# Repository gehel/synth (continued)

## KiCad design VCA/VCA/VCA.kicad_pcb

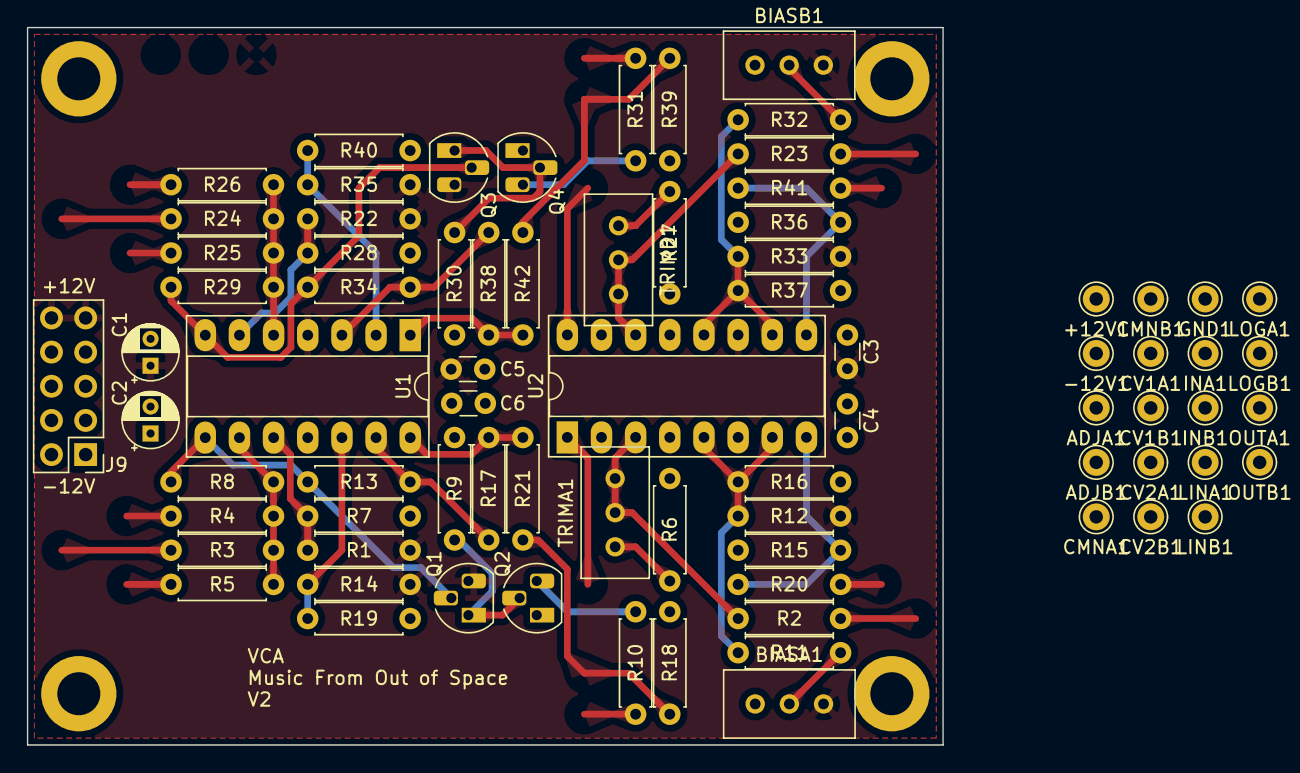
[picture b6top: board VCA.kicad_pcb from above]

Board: 4 copper layers, 68.1 x 53.3 mm, 82 parts (0 on the bottom side), 45 nets.

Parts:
+12V1: Conn_01x01_Pin; Pin_D1.0mm_L10.0mm
-12V1: Conn_01x01_Pin; Pin_D1.0mm_L10.0mm
ADJA1: Conn_01x01_Pin; Pin_D1.0mm_L10.0mm
ADJB1: Conn_01x01_Pin; Pin_D1.0mm_L10.0mm
BIASA1: 100K; Potentiometer_Bourns_3296W_Vertical
BIASB1: 100K; Potentiometer_Bourns_3296W_Vertical
C1, C2: 10uF; CP_Radial_D4.0mm_P2.00mm
C3, C4, C5, C6: 100nF; C_Disc_D3.0mm_W1.6mm_P2.50mm
CMNA1: Conn_01x01_Pin; Pin_D1.0mm_L10.0mm
CMNB1: Conn_01x01_Pin; Pin_D1.0mm_L10.0mm
CV1A1, CV1B1, CV2A1, CV2B1: Conn_01x01_Pin; Pin_D1.0mm_L10.0mm
GND1: Conn_01x01_Pin; Pin_D1.0mm_L10.0mm
H1, H2, H3, H4: MountingHole_Pad; MountingHole_3.2mm_M3_DIN965_Pad
INA1: Conn_01x01_Pin; Pin_D1.0mm_L10.0mm
INB1: Conn_01x01_Pin; Pin_D1.0mm_L10.0mm
J9: Conn_02x05_Odd_Even; PinHeader_2x05_P2.54mm_Vertical
LINA1: Conn_01x01_Pin; Pin_D1.0mm_L10.0mm
LINB1: Conn_01x01_Pin; Pin_D1.0mm_L10.0mm
LOGA1: Conn_01x01_Pin; Pin_D1.0mm_L10.0mm
LOGB1: Conn_01x01_Pin; Pin_D1.0mm_L10.0mm
OUTA1: Conn_01x01_Pin; Pin_D1.0mm_L10.0mm
OUTB1: Conn_01x01_Pin; Pin_D1.0mm_L10.0mm
Q1, Q3: 2N3904; TO-92_HandSolder
Q2, Q4: 2N3906; TO-92_HandSolder
R1, R2, R3, R4, R5, R14, R17, R19, R22, R23, R24, R25, R26, R35, R38, R40: 100K; R_Axial_DIN0207_L6.3mm_D2.5mm_P7.62mm_Horizontal
R6, R27: 150R; R_Axial_DIN0207_L6.3mm_D2.5mm_P7.62mm_Horizontal
R7, R8, R13, R28, R29, R34: 2K; R_Axial_DIN0207_L6.3mm_D2.5mm_P7.62mm_Horizontal
R9, R30: 120K; R_Axial_DIN0207_L6.3mm_D2.5mm_P7.62mm_Horizontal
R10, R18, R31, R39: 20K; R_Axial_DIN0207_L6.3mm_D2.5mm_P7.62mm_Horizontal
R11, R32: 2M; R_Axial_DIN0207_L6.3mm_D2.5mm_P7.62mm_Horizontal
R12, R33: 470K; R_Axial_DIN0207_L6.3mm_D2.5mm_P7.62mm_Horizontal
R15, R36: 4.7K; R_Axial_DIN0207_L6.3mm_D2.5mm_P7.62mm_Horizontal
R16, R37: 47K; R_Axial_DIN0207_L6.3mm_D2.5mm_P7.62mm_Horizontal
R20, R41: 1K; R_Axial_DIN0207_L6.3mm_D2.5mm_P7.62mm_Horizontal
R21, R42: 30K; R_Axial_DIN0207_L6.3mm_D2.5mm_P7.62mm_Horizontal
TRIMA1: 2K; Potentiometer_Bourns_3296W_Vertical
TRIMB1: 2K; Potentiometer_Bourns_3296W_Vertical
U1: TL084; DIP-14_W7.62mm_Socket_LongPads
U2: LM13700; DIP-16_W7.62mm_Socket_LongPads

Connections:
+12V: +12V1.1, BIASA1.1, BIASB1.1, C1.1, C3.1, C5.1, J9.9, J9.10, Q1.3 (C), Q3.3 (C), R1.1, R12.1, R14.1, R22.1, R33.1, R35.1, U1.4 (V+), U2.11 (V+)
-12V: -12V1.1, BIASA1.3, BIASB1.3, C2.2, C4.2, C6.2, J9.1, J9.2, R9.1, R15.1, R18.1, R30.1, R36.1, R39.1, U1.11 (V-), U2.6 (V-)
ADJA: ADJA1.1, R5.1
ADJB: ADJB1.1, R26.1
CMNA: CMNA1.1, U2.1
CMNB: CMNB1.1, U2.16
CV1A: CV1A1.1, R3.1
CV1B: CV1B1.1, R24.1
CV2A: CV2A1.1, R4.1
CV2B: CV2B1.1, R25.1
GND: C1.2, C2.1, C3.2, C4.1, C5.2, C6.1, GND1.1, H1.1, H2.1, H3.1, H4.1, J9.3, J9.4, J9.5, J9.6, J9.7, J9.8, Q2.1 (E), Q4.1 (E), R6.1, R7.2, R16.2, R19.2, R27.1, R28.2, R37.2, R40.2, U2.4 (-), U2.13 (-)
INA: INA1.1, R2.1
INB: INB1.1, R23.1
LINA: LINA1.1, R18.2, R21.1
LINB: LINB1.1, R39.2, R42.1
LOGA: LOGA1.1, R10.1
LOGB: LOGB1.1, R31.1
unnamed: BIASA1.2, R11.1
unnamed: BIASB1.2, R32.1
unnamed: Q1.2 (B), R8.2, R13.1, U1.8
unnamed: Q1.1 (E), Q2.2 (B), R9.2
unnamed: Q2.3 (C), R10.2
unnamed: Q3.2 (B), R29.2, R34.1, U1.7
unnamed: Q3.1 (E), Q4.2 (B), R30.2
unnamed: Q4.3 (C), R31.2
unnamed: R6.2, TRIMA1.3
unnamed: R11.2, R12.2, R16.1, U2.5, U2.7
unnamed: R15.2, R20.1, U2.8
unnamed: R17.2, R21.2, U1.14
unnamed: R27.2, TRIMB1.3
unnamed: R32.2, R33.2, R37.1, U2.10, U2.12
unnamed: R36.2, R41.1, U2.9
unnamed: R38.2, R42.2, U1.1
unnamed: R34.2, R38.1, U1.3 (+)
unnamed: R35.2, R40.1, U1.2 (-)
unnamed: R24.2, R25.2, R26.2, R29.1, U1.5 (+)
unnamed: R22.2, R28.1, U1.6 (-)
unnamed: R1.2, R7.1, U1.10 (+)
unnamed: R3.2, R4.2, R5.2, R8.1, U1.9 (-)
unnamed: R14.2, R19.1, U1.12 (+)
unnamed: R13.2, R17.1, U1.13 (-)
unnamed: R23.2, TRIMB1.1, TRIMB1.2, U2.14 (+)
unnamed: R2.2, TRIMA1.1, TRIMA1.2, U2.3 (+)
OUTA: OUTA1.1, R20.2
OUTB: OUTB1.1, R41.2

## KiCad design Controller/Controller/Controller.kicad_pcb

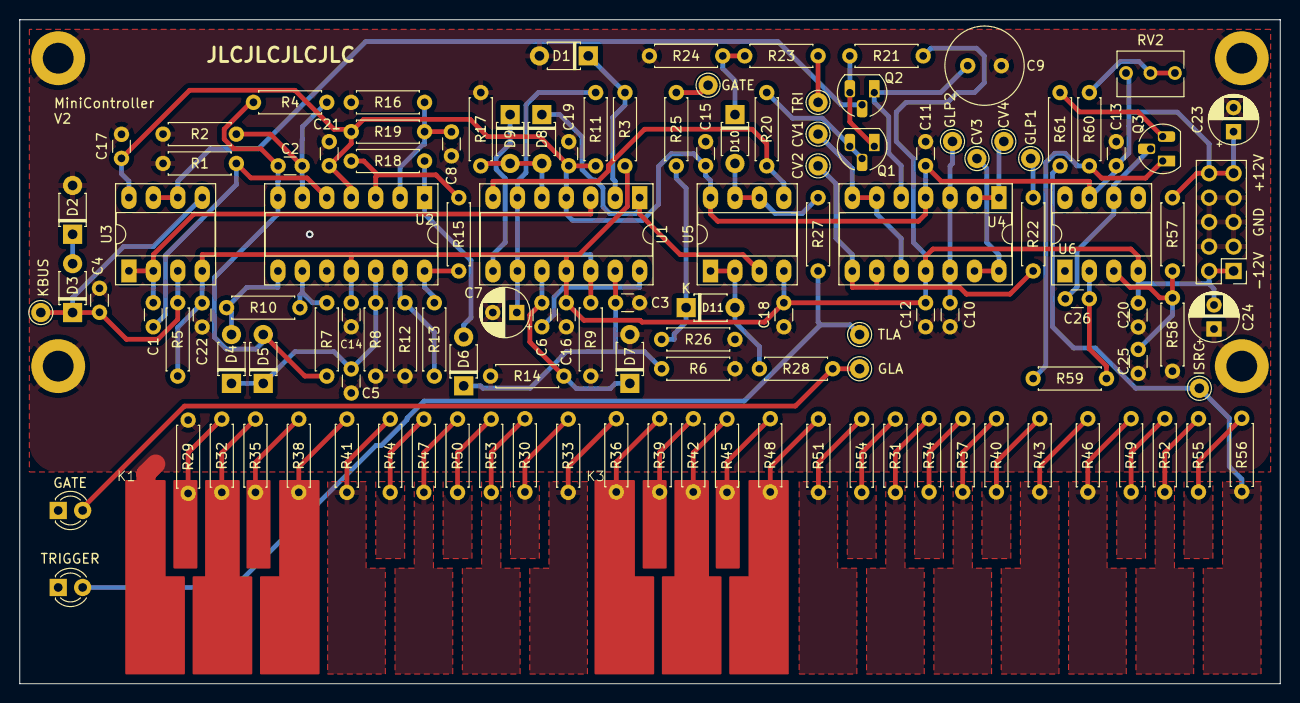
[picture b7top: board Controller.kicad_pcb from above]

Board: 2 copper layers, 131.0 x 69.0 mm, 129 parts (0 on the bottom side), 78 nets.

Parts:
C1: 1nF; C_Disc_D3.0mm_W1.6mm_P2.50mm
C2: 22pF; C_Disc_D3.0mm_W1.6mm_P2.50mm
C3, C6: 4.7nF; C_Disc_D3.0mm_W1.6mm_P2.50mm
C4, C5: 470pF; C_Disc_D3.0mm_W1.6mm_P2.50mm
C7, C23, C24: 10uF; CP_Radial_D5.0mm_P2.50mm
C8, C10, C11, C12, C13, C14, C15, C16, C17, C18, C19, C20, C21, C22, C25: 100nF; C_Disc_D3.0mm_W1.6mm_P2.50mm
C9: 10nF; C_Radial_D8.0mm_H11.5mm_P3.50mm
C26: 10nF; C_Disc_D3.0mm_W1.6mm_P2.50mm
D1, D2, D3, D4, D5, D6, D7, D8, D9, D10, D11: 1N914; D_T-1_P5.08mm_Horizontal
D12: TRIG; LED_D3.0mm
D13: GATE; LED_D3.0mm
H1, H2, H3, H4: MountingHole_Pad; MountingHole_3.2mm_M3_DIN965_Pad
J1: Conn_02x05_Odd_Even; PinHeader_2x05_P2.54mm_Vertical
J2, J3, J4, J5, J6, J7, J8, J9, J10, J11, J12, J13: Conn_01x01_Pin; Pin_D1.0mm_L10.0mm
K1, K3: Keyboard 5 keys
Q1, Q2: 2N5457; TO-92_HandSolder
Q3: 2N3906; TO-92_HandSolder
R1: 30K; R_Axial_DIN0207_L6.3mm_D2.5mm_P7.62mm_Horizontal
R2: 4.7K; R_Axial_DIN0207_L6.3mm_D2.5mm_P7.62mm_Horizontal
R3, R4, R5, R8, R18, R59: 1M; R_Axial_DIN0207_L6.3mm_D2.5mm_P7.62mm_Horizontal
R6: 300K; R_Axial_DIN0207_L6.3mm_D2.5mm_P7.62mm_Horizontal
R7, R10: 10k; R_Axial_DIN0207_L6.3mm_D2.5mm_P7.62mm_Horizontal
R9, R11, R19: 100K; R_Axial_DIN0207_L6.3mm_D2.5mm_P7.62mm_Horizontal
R12: 10K; R_Axial_DIN0207_L6.3mm_D2.5mm_P7.62mm_Horizontal
R13, R24, R26: 20K; R_Axial_DIN0207_L6.3mm_D2.5mm_P7.62mm_Horizontal
R14, R21: 200K; R_Axial_DIN0207_L6.3mm_D2.5mm_P7.62mm_Horizontal
R15: 100k; R_Axial_DIN0207_L6.3mm_D2.5mm_P7.62mm_Horizontal
R16: 150K; R_Axial_DIN0207_L6.3mm_D2.5mm_P7.62mm_Horizontal
R17: 47K; R_Axial_DIN0207_L6.3mm_D2.5mm_P7.62mm_Horizontal
R20, R57: 39K; R_Axial_DIN0207_L6.3mm_D2.5mm_P7.62mm_Horizontal
R22: 20R; R_Axial_DIN0207_L6.3mm_D2.5mm_P7.62mm_Horizontal
R23, R25: 1K; R_Axial_DIN0207_L6.3mm_D2.5mm_P7.62mm_Horizontal
R27, R28: 3K; R_Axial_DIN0207_L6.3mm_D2.5mm_P7.62mm_Horizontal
R29, R30, R31, R32, R33, R34, R35, R36, R37, R38, R39, R40, R41, R42, R43, R44, R45, R46, R47, R48, R49, R50, R51, R52, R53, R54, R55, R56: 100R; R_Axial_DIN0207_L6.3mm_D2.5mm_P7.62mm_Horizontal
R58: 82K; R_Axial_DIN0207_L6.3mm_D2.5mm_P7.62mm_Horizontal
R60, R61: 3.9K; R_Axial_DIN0207_L6.3mm_D2.5mm_P7.62mm_Horizontal
RV2: 1K; Potentiometer_Bourns_3266Y_Vertical
U1, U2: TL074; DIP-14_W7.62mm_Socket_LongPads
U3, U5: TL072; DIP-8_W7.62mm_Socket_LongPads
U4: LF444; DIP-14_W7.62mm_Socket_LongPads
U6: TL071; DIP-8_W7.62mm_Socket_LongPads

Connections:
+12V: C11.1, C13.1, C15.1, C17.1, C19.1, C21.1, C23.1, J1.9, J1.10, R11.1, R19.1, R57.2, RV2.3, U1.4 (V+), U2.4 (V+), U3.8 (V+), U4.4 (V+), U5.8 (V+), U6.7 (V+)
-12V: C12.2, C14.2, C16.2, C18.2, C20.2, C22.2, C24.2, J1.1, J1.2, R3.1, R5.2, R21.2, U1.11 (V-), U2.11 (V-), U3.4 (V-), U4.11 (V-), U5.4 (V-), U6.4 (V-)
CV1: J2.1, U4.6 (-), U4.7, U4.10 (+)
CV2: J3.1, R22.1, U4.8, U4.9 (-)
CV3: J4.1, U4.13 (-), U4.14
CV4: J5.1, U4.1, U4.2 (-)
GATE: J6.1, R25.1
GLA: D13.2 (A), J10.1, R28.1
GLP1: J8.1, R22.2
GLP2: C10.1, J9.1, U4.3 (+), U4.12 (+)
GND: C3.1, C4.2, C5.1, C7.2, C8.1, C9.2, C10.2, C11.2, C12.1, C13.2, C14.1, C15.2, C16.1, C17.2, C18.1, C19.2, C20.1, C21.2, C22.1, C23.2, C24.1, C25.2, D1.2 (A), D2.2 (A), D7.2 (A), D12.1 (K), D13.1 (K), H1.1, H2.1, H3.1, H4.1, J1.3, J1.4, J1.5, J1.6, J1.7, J1.8, K1.1 (C), R1.2, R2.2, R6.2, R8.2, R9.2, R12.2, R14.2, R16.2, R17.2, R24.1, R26.1, R29.1, R58.1, U2.10 (+)
ISRC: J13.1, R56.2, R61.1
K2: K1.2 (C#), R29.2, R32.1
K3: K1.3 (D), R32.2, R35.1
K4: K1.4 (D#), R35.2, R38.1
K5: K1.5 (E), R38.2, R41.1
K6: R41.2, R44.1
K7: R44.2, R47.1
K8: R47.2, R50.1
K9: R50.2, R53.1
K10: R30.1, R53.2
K11: R30.2, R33.1
K12: R33.2, R36.1
K13: K3.1 (C), R36.2, R39.1
K14: K3.2 (C#), R39.2, R42.1
K15: K3.3 (D), R42.2, R45.1
K16: K3.4 (D#), R45.2, R48.1
K17: K3.5 (E), R48.2, R51.1
K18: R51.2, R54.1
K19: R31.1, R54.2
K20: R31.2, R34.1
K21: R34.2, R37.1
K22: R37.2, R40.1
K23: R40.2, R43.1
K24: R43.2, R46.1
K25: R46.2, R49.1
K26: R49.2, R52.1
K27: R52.2, R55.1
K28: R55.2, R56.1
KBUS: C4.1, D3.1 (K), J12.1, R5.1, U3.3 (+), U3.5 (+)
unnamed: C6.1, U1.14
unnamed: D1.1 (K), R3.2, U1.2 (-)
unnamed: D2.1 (K), D3.2 (A)
unnamed: D4.2 (A), R10.1, U2.8
unnamed: C5.2, D4.1 (K), D5.1 (K), R8.1, U2.12 (+)
unnamed: C2.2, D5.2 (A), R4.1, R7.2, U2.7
unnamed: D6.2 (A), R18.1, U2.1
unnamed: C3.2, D6.1 (K), R6.1, U1.13 (-)
unnamed: C6.2, D7.1 (K), R14.1, U1.10 (+)
unnamed: D8.2 (A), D9.2 (A), R17.1, U1.5 (+)
unnamed: D8.1 (K), U1.1, U5.3 (+)
unnamed: D9.1 (K), U1.8
unnamed: D10.2 (A), R27.2, U5.6 (-), U5.7
unnamed: D10.1 (K), R23.2, R24.2
unnamed: D11.2 (A), R28.2, U5.1, U5.2 (-)
unnamed: D11.1 (K), R25.2, R26.2
unnamed: Q1.1 (D), Q2.3 (G), R21.1
unnamed: Q1.2 (S), Q1.3 (G), R20.1
unnamed: C9.1, Q2.1 (D), U4.5 (+)
unnamed: Q2.2 (S), U3.6 (-), U3.7
unnamed: C26.2, Q3.2 (B), U6.6
unnamed: Q3.3 (C), R61.2
unnamed: Q3.1 (E), R59.1, R60.2
unnamed: R13.1, R15.2, U2.14
unnamed: R60.1, RV2.1, RV2.2
unnamed: C1.1, U1.3 (+), U3.1, U3.2 (-)
unnamed: C7.1, R9.1, R11.2, U1.6 (-), U1.9 (-), U1.12 (+)
unnamed: R15.1, R18.2, U2.3 (+)
unnamed: C8.2, R16.1, R19.2, U2.2 (-)
unnamed: C1.2, R1.1, U2.5 (+)
unnamed: C2.1, R2.1, R4.2, U2.6 (-)
unnamed: R7.1, R10.2, U2.9 (-)
unnamed: R12.1, R13.2, U2.13 (-)
unnamed: R20.2, U1.7, U5.5 (+)
unnamed: C25.1, R57.1, R58.2, U6.3 (+)
unnamed: C26.1, R59.2, U6.2 (-)
TLA: D12.2 (A), J11.1, R27.1
TRIG: J7.1, R23.1

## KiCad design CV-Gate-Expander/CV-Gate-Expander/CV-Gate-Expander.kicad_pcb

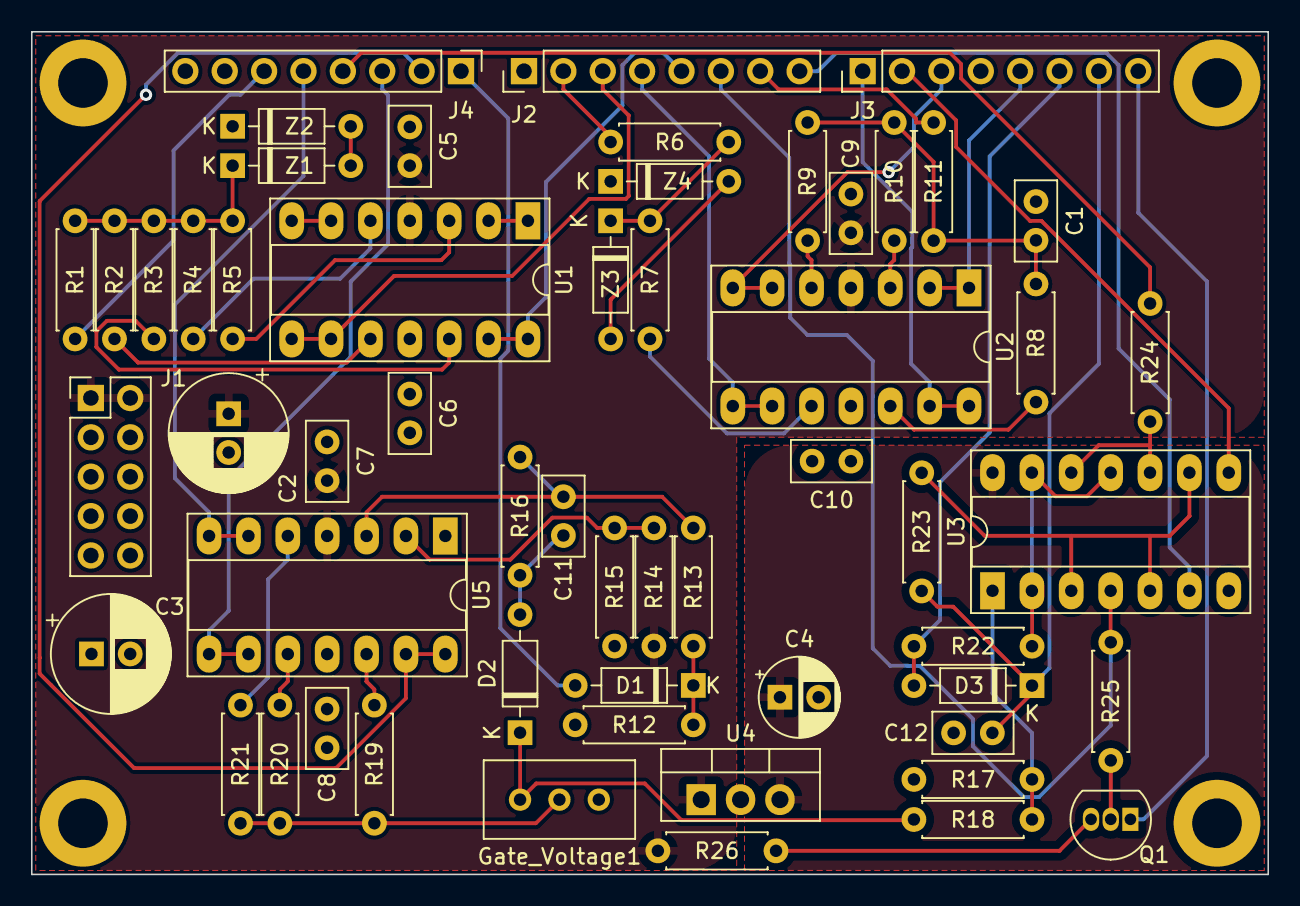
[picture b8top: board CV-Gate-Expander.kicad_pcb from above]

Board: 4 copper layers, 79.8 x 54.4 mm, 60 parts (0 on the bottom side), 54 nets.

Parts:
C1, C12: 220nF; C_Disc_D5.0mm_W2.5mm_P2.50mm
C2, C3: 10uF; CP_Radial_D7.5mm_P2.50mm
C4: 1uF; CP_Radial_D5.0mm_P2.50mm
C5, C6, C7, C8, C9, C10: 100nF; C_Disc_D5.0mm_W2.5mm_P2.50mm
C11: 47pF; C_Disc_D5.0mm_W2.5mm_P2.50mm
D1, D2, D3: 1N914; D_DO-35_SOD27_P7.62mm_Horizontal
Gate_Voltage1: 100K; Potentiometer_Bourns_3296W_Vertical
H1, H2, H3, H4: MountingHole_Pad; MountingHole_3.2mm_M3_DIN965_Pad
J1: Conn_02x05_Odd_Even; PinHeader_2x05_P2.54mm_Vertical
J2, J3, J4: Conn_01x08; PinHeader_1x08_P2.54mm_Vertical
Q1: 2N3904; TO-92_Inline
R1, R2, R3, R4, R5, R6, R7, R8, R9, R10, R19, R20, R21: 10K; R_Axial_DIN0207_L6.3mm_D2.5mm_P7.62mm_Horizontal
R11, R22: 100R; R_Axial_DIN0207_L6.3mm_D2.5mm_P7.62mm_Horizontal
R12, R14, R17, R25: 100K; R_Axial_DIN0207_L6.3mm_D2.5mm_P7.62mm_Horizontal
R13, R15: 20K; R_Axial_DIN0207_L6.3mm_D2.5mm_P7.62mm_Horizontal
R16: 1M; R_Axial_DIN0207_L6.3mm_D2.5mm_P7.62mm_Horizontal
R18: 130K; R_Axial_DIN0207_L6.3mm_D2.5mm_P7.62mm_Horizontal
R23: 1K; R_Axial_DIN0207_L6.3mm_D2.5mm_P7.62mm_Horizontal
R24, R26: 2K; R_Axial_DIN0207_L6.3mm_D2.5mm_P7.62mm_Horizontal
U1, U2, U5: TL074; DIP-14_W7.62mm_Socket_LongPads
U3: 40106; DIP-14_W7.62mm_Socket_LongPads
U4: LM7805_TO220; TO-220-3_Vertical
Z1, Z2, Z3, Z4: 1N5231B; D_DO-35_SOD27_P7.62mm_Horizontal

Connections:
+5V: C4.1, U3.14 (VDD), U4.3 (VO)
+12V: C2.1, C5.2, C7.2, C9.2, J1.1, J1.2, R14.2, R26.2, U1.4 (V+), U2.4 (V+), U4.1 (VI), U5.4 (V+)
-12V: C3.2, C6.1, C8.1, C10.1, J1.9, J1.10, U1.11 (V-), U2.11 (V-), U5.11 (V-)
GND: C1.1, C2.2, C3.1, C4.2, C5.1, C6.2, C7.1, C8.2, C9.1, C10.2, C12.1, Gate_Voltage1.3, H1.1, H2.1, H3.1, H4.1, J1.3, J1.4, J1.5, J1.6, J1.7, J1.8, J2.1, R12.1, R15.1, R17.2, U3.7 (VSS), U4.2 (GND), Z2.1 (K), Z4.1 (K)
NG: R22.2, U3.2, U3.11, U3.13
unnamed: C1.2, R8.1, R9.1, R10.1, R11.1
unnamed: D1.1 (K), R12.2, R13.1
unnamed: C11.2, D2.2 (A), R16.2, U5.1
unnamed: D2.1 (K), Gate_Voltage1.1, R18.1
unnamed: Gate_Voltage1.2, R19.2, R20.2, R21.2
unnamed: Q1.2 (B), R25.1
unnamed: Q1.3 (C), R26.1
unnamed: R17.1, R18.2, U3.1
unnamed: R23.1, U3.3, U3.5, U3.9
unnamed: R24.2, U3.10, U3.12
unnamed: R5.2, U1.3 (+)
unnamed: U1.1, U1.2 (-)
unnamed: R4.2, U1.5 (+)
unnamed: U1.6 (-), U1.7
unnamed: R2.2, U1.10 (+)
unnamed: R3.2, U1.12 (+)
unnamed: R10.2, U2.3 (+)
unnamed: R9.2, U2.5 (+)
unnamed: R7.2, U2.10 (+)
unnamed: R8.2, U2.12 (+)
unnamed: C11.1, R13.2, R16.1, U5.3 (+)
unnamed: R14.1, R15.2, U5.2 (-)
unnamed: R21.1, U5.5 (+)
unnamed: R20.1, U5.10 (+)
unnamed: R19.1, U5.12 (+)
unnamed: Z1.2 (A), Z2.2 (A)
unnamed: R1.2, R2.1, R3.1, R4.1, R5.1, Z1.1 (K)
unnamed: Z3.2 (A), Z4.2 (A)
unnamed: R6.2, R7.1, Z3.1 (K)
X1: J2.2, R6.1
X2: J2.3, U1.8, U1.9 (-)
X3: J2.4, U2.8, U2.9 (-)
X4: J2.5, U1.13 (-), U1.14
X5: J2.6, R25.2, U3.4
X6: J2.7, R11.2
X8: J2.8, U3.6
X9: J3.1, U2.13 (-), U2.14
X10: J3.2, U3.8
X11: J3.3, U2.6 (-), U2.7
X13: J3.5, U2.1, U2.2 (-)
X14: D3.2 (A), J3.6, R22.1
X15: C12.2, D3.1 (K), J3.7, R23.2
X16: J3.8, Q1.1 (E)
X17: D1.2 (A), J4.1
X18: J4.2, U5.13 (-), U5.14
X19: J4.3, U5.8, U5.9 (-)
X20: J4.4, R24.1
X21: J4.5, U5.6 (-), U5.7
X22: J4.6, R1.1

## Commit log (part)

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2023-10-04 misc
2023-10-16 some silkscreen helpers
2023-10-16 first version of a VCO panel
2023-10-17 split VCO controls plane in separate project
2023-10-18 mounting holes
2023-10-18 first partial version of VCA
2023-10-18 add .gitignore file
2023-10-19 VCA PCB completed
2023-10-19 VCA panel completed
2023-10-19 LFO schematic
2023-10-20 gerber params
2023-10-20 added missing connectors
2023-10-26 most of PCB done
2023-10-27 corrected capacitor sizes in bom
2023-10-27 added pwr connection to control board
2023-10-27 schematic for LFO control board
2023-10-28 first LFO panel version
2023-10-28 LFO panel, not fully routed
2023-10-28 LFO controls completed
2023-10-28 LFO panel: add jlcpcb project file
2023-10-28 git ignore: production directories
2023-10-31 half done controller
2023-11-01 controller almost routed
2023-11-02 controller routed
2023-11-02 sequencer started
2023-11-02 start of panel script
2023-11-02 just playing around
2023-11-03 autogeneration of 1P12T footprint
2023-11-03 adding connectors to sequencer
2023-11-08 bracket to mount LFO
2023-11-08 footprint for 3P4T rotary switch
2023-11-08 ignore STL and Freecad files
2023-11-08 Grounding to pot
2023-11-08 minor fixes after first build
2023-11-08 Sequencer control fully routed
2023-11-08 minor cleanup of silkscreen
2023-11-08 moved to 4 layers
2023-11-08 add grounding to potentiometer
2023-11-08 created empty sequencer panel
2023-11-08 initial sequencer main board
2023-11-08 added caches to .gitignore
2023-11-11 Alien Screamer - partial
2023-11-13 Alien Screamer - nicer looking - cap sizes
2023-11-14 Added 3d models
2023-11-15 misc sequencer
2023-11-15 Alien Screamer - changing resistor's sizes
2023-11-15 controller - changed resistor sizes
2023-11-16 controller routed with correct resistor sizes
2023-11-16 Alien Screamer - add teardrops
2023-11-17 minor
2023-11-17 minor progress on sequencer
2023-11-17 Sequencer - schematic mostly complete
2023-11-20 Sequencer control - minor
2023-11-20 Sequencer - minor progress on routing
2023-11-20 Alien Screamer - changed resistors sizes
2023-11-20 Sequencer - mostly positionned
2023-11-20 Sequencer - autorouted
2023-11-20 Alien Screamer - added teardrops
2023-11-20 Controller - minor clean up
2023-11-21 Noise - PCB ready
2023-11-24 VCF 12db/oct
2023-11-24 VCF - fully routed
2023-11-26 mixer - starting
2023-11-26 minor cleanup
2023-11-26 VCA - correct resistors sizes
2023-11-27 VCO - changed resistors size
2023-11-27 VCF - add teardrops
2023-11-27 VCF - panel and controls
2023-11-27 Noise - cleanup
2023-11-27 Noise - panel and controls
2023-12-07 footprint for dual gang pot
2023-12-07 Mixer - misc
2023-12-07 Sequencer - misc
2023-12-07 CV Gate Expander - first draft
2023-12-07 AlienScream - fixed a few values
2023-12-07 Alien Screamer - misc fixes
2023-12-07 Alien Screamer - add interactive bom
2023-12-10 minor fixes and cleanups
2023-12-14 Controller - minor fixes
2023-12-14 Controller - PCB cleanup
2023-12-19 VCO - fixes
2023-12-20 Controller - incomplete fixes
2023-12-20 Noise Toaster
2023-12-20 Alien Screamer - fix audio jack
2023-12-23 VCA - updated trim pot footprint, partial fix
2023-12-24 Alien Screamer - fix switch orientation and remove optional components
2023-12-27 Noise - minor fix
2023-12-28 Noise Toaster - fixes after first board
2023-12-30 Alien Screamer - increase version
2024-01-09 added kibot integration for Alien Screamer
2024-01-09 fixed workflow
2024-01-09 fixed library path
2024-01-09 migrate libraries
2024-01-09 checkout 3 last commits for diffs
2024-01-09 outputs in the right path
2024-01-09 full checkout during CI
2024-07-12 VCF - fix some components value
2024-09-11 JLCPCB order number template
2024-09-11 VCO cleanup board
2025-01-10 clear queue
2026-04-11 added blank kicad project
2026-04-15 cleanup
